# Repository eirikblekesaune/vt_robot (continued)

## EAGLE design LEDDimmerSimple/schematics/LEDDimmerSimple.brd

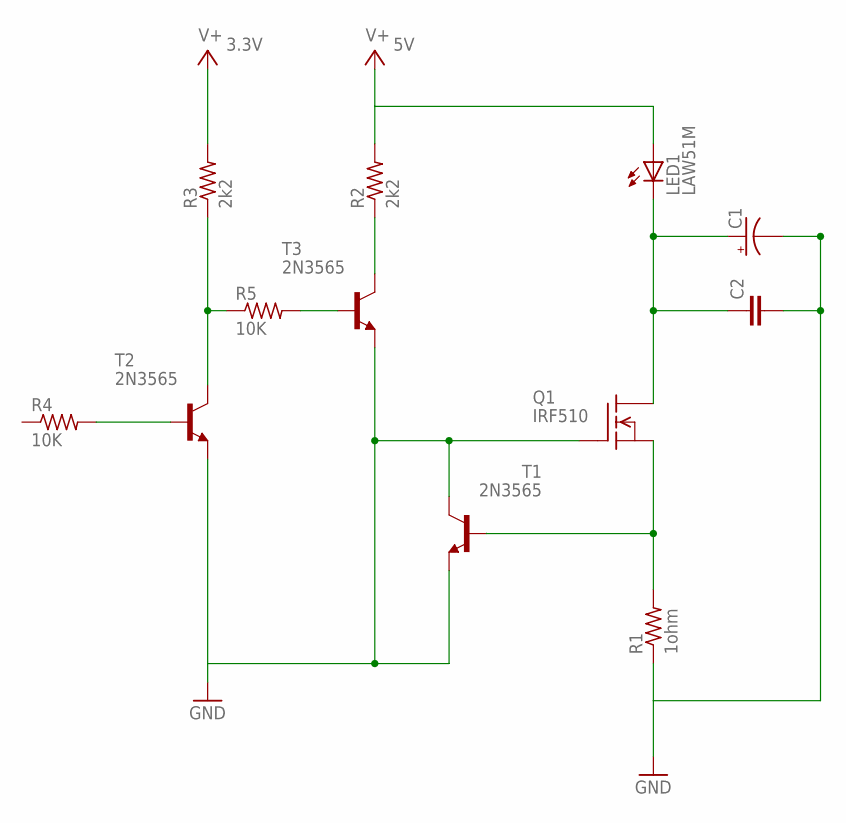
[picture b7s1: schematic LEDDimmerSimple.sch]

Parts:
C1: CPOL-USE1.8-4; E1,8-4
C2: C-EU025-030X050; C025-030X050
LED1: LAW51M; W51
Q1: IRF510; TO220
R1: 1ohm; P0613V
R2, R3: 2k2; 0207/7
R4, R5: 10K; 0207/7
T1, T2, T3: 2N3565; TO92

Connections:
GND: C1.-, C2.2, Q1.1 (G), R1.1, T1.1 (C), T1.3 (E), T2.3 (E), T3.3 (E)
unnamed: R3.1, R5.1, T2.1 (C)
unnamed: R4.2, T2.2 (B)
unnamed: R5.2, T3.2 (B)
unnamed: R2.1, T3.1 (C)
unnamed: C1.+, C2.1, LED1.C, Q1.2 (D)
unnamed: Q1.3 (S), R1.2, T1.2 (B)
V+: LED1.A, R2.2, R3.2

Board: 2 copper layers, 12 parts (0 on the bottom side), 8 nets, no tracks yet.

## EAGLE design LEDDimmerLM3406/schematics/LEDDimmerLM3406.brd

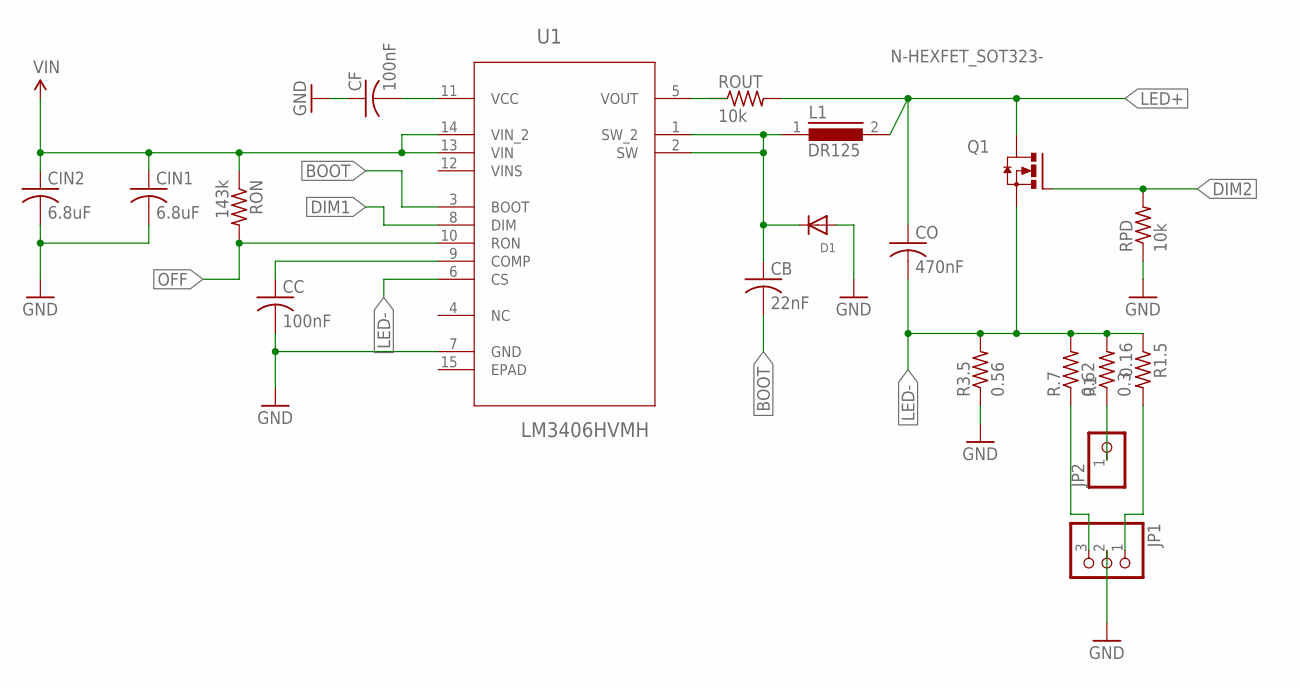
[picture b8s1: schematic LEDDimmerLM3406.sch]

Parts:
CB: 22nF; C0603
CC: 100nF; C0603
CF: 100nF; C0603
CIN1, CIN2: 6.8uF; C1812
CO: 470nF; C1206
D1: DIODESMA; SMADIODE
JP1: PINHD-1X3; 1X03
JP2: PINHD-1X1; 1X01
L1: DR125
Q1: N-HEXFET_SOT323-; SOT223
R1: 0.3; R0805
R1.5: 0.16; R0805
R3.5: 0.56; R0805
R.7: 0.62; R0805
RON: 143k; R0805
ROUT: 10k; R0603
RPD: 10k; R0603
U1: LM3406HVMH; SOP65P640X110-15N

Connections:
BOOT: CB.2, U1.3 (BOOT)
DIM1: U1.8 (DIM)
DIM2: Q1.1 (G), RPD.2
GND: CC.2, CF.1, CIN1.2, CIN2.2, D1.A, JP1.2, R3.5.1, RPD.1, U1.7 (GND)
LED+: CO.1, L1.2, Q1.4 (D), ROUT.2
LED-: CO.2, Q1.3 (S), R1.2, R1.5.1, R3.5.2, R.7.2, U1.6 (CS)
unnamed: CC.1, U1.9 (COMP)
unnamed: CF.2, U1.11 (VCC)
unnamed: CB.1, D1.C, L1.1, U1.1 (SW_2), U1.2 (SW)
unnamed: JP1.3, R.7.1
unnamed: JP1.1, R1.5.2
unnamed: JP2.1, R1.1
OFF: RON.2, U1.10 (RON)
VIN: CIN1.1, CIN2.1, RON.1, U1.13 (VIN), U1.14 (VIN_2)

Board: 2 copper layers, 19 parts (0 on the bottom side), 13 nets, no tracks yet.

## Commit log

2013-04-03 First commit of Arduino sketches
2013-04-03 first pinne commit
2013-04-03 Moved pinne robot into own folder
2013-04-03 Added .gitignore
2013-04-03 Removed useless DS_Store
2013-04-24 bird two with drv8825 stepper and OSC working
2013-04-24 Added lib folder for external libraries
2013-07-08 Started working on new pinnerobot code.
2013-07-08 Only need two byte for value messages
2013-07-09 Update for working with pinnerobot
2013-07-09 Deleted old unused files
2013-07-09 Backup after tragic crash..
2013-07-09 Restoration after crash.
2013-07-09 Added get handlers for left motor commands
2013-07-09 PinneRobot: Fixed direction setting and sematics
2013-07-10 Moving motors into separate classes
2013-07-10 Migrating into C++ style
2013-07-10 Deleted unused files
2013-07-10 Sync before merge
2013-07-10 Backing up files
2013-07-10 Nuther backup
2013-07-10 Removing unused files.
2013-07-10 Fixed:Starting and stoping left motors
2013-07-10 Changed debugging to macros.
2013-07-10 PinneRobot: Reply to get commands
2013-08-13 Moved PinneProtocol.md file
2013-08-13 Updated protocol doc, added parser/api for SC
2013-08-14 API comm with getter and setters. closes #2
2013-08-14 Enabled state change reporting aggin
2013-08-14 Removed and remapped current sense pins for VNH5019 driver.
2013-08-19 Changed defines to consts
2013-09-06 Added pinne and tog patch and classes for monsterbox
2013-09-06 Changed input scaling for pinner og tog. Added one wrieless LED
2013-09-09 An update in case Arduino.app want do somethin awful again.
2013-09-09 Please enter the commit message for your changes. Lines starting PinneMotor logic now works.
2013-09-10 Added rotation motor control with high freq PWM on timer3
2013-09-10 Update on rotation motor implementation. Still to figure the logic for bounds checking and target stopping.
2013-09-17 Added lots of stuff. In two files. Which in not a of stuff.. These commit messages are really testing my creativity.
2013-09-17 Added LEDDimmer fade sketch
2013-09-18 More fixes on the pinnne trobot. Rotation logic almost in place.
2013-09-18 Rotation motor logic in pinnerobot now works, but untested.
2013-09-18 Allow setting currentPosition for pinne motors, since they are relative.
2013-09-18 Failed attempt to add EEPROM setting storage.
2013-09-20 Added OSC responder for fuglen.
2013-09-20 Logic for pinnerobot now works. Still some hickups with starting in park position.
2013-09-20 Started implementing PID control for rotation motor in pinne robot
2013-09-22 Added API and setter/getters for PID control parameters.
2013-09-22 Removed PID control in pinne robot and started implementing standard ease inout class.
2013-09-23 Backup, table lookup sine ramping for targeting in robot pinne
2013-09-23 Some kind of ease ramping function for motors in pinne robot
2013-09-23 Fixed stupid little bug.
2013-09-23 Last update for the evening
2013-09-30 Started making class for pinne robot
2013-10-01 Backup
2013-10-15 Pre merge commit Bontelabo
2013-10-15 Bontalabo update day 2
2013-10-15 Found correct serial port addresses for pinner,
2013-10-27 Bontelabo update for pinner
2013-10-27 Backup before leaving Bontelabo
2013-11-18 Small update to pinne protocol
2013-11-18 Added lokomotiv folder
2013-12-05 Moved PinneRobot project into ino project
2013-12-06 KampenTokyo update
2013-12-06 Added configuration seup to pinne arduino prject
2013-12-06 Text reformatting of robot SC classes
2013-12-07 Added different debounce for slack and top sensor
2013-12-07 Som work on pinne SC classes
2013-12-22 Initial Kopprobot commit
2013-12-22 .gitignore for KoppRobot
2013-12-22 gitignore removals
2013-12-23 Added outline structure
2014-01-09 New year update 2014
2014-01-17 Lokootiv can now parse IR incoming adrres
2014-01-17 .swo removal
2014-01-27 Filename change
2014-02-11 Added schematics for three robots: Kopp, Lokomotiv and IRBeacon
2014-02-11 Added two LED dimmer schematics
2014-03-03 Pinne fixes
2014-03-03 Basic funcationalit for new pinne classes
2014-04-01 More pinne fix and circuit stuff
2014-04-01 Deleted old version of IRBeacon
2014-04-13 gitignore chagne
2014-04-13 EnkelFugl and some circuit changes
2014-04-14 Clasifiing fugle and stepper classes
2014-04-14 Removed DSStore file
2014-04-14 Chassis label for Kopprrobot
2014-04-15 Bugsquashing
2014-04-22 First workin IRBeacon version with etched circuit
2014-04-22 No hex or elf files in rep
2014-04-22 Changes and additions etc.
2014-04-30 Fixed clock setting
2014-04-30 PRe new Kopp roboter
2014-05-02 Added kopp robot simple with walk in mekanikkpatch
2014-05-06 Added fotbrett scehmatic
2014-05-06 Fixed inverting port vals in IRBeaocn
2014-05-06 Fxied invertion IRBeacon again
2014-05-09 Some work on Lokomotiv. Speed interpolation.
2014-05-21 XBeeProfiles for xctung application
2014-05-21 Updates in general
2014-05-21 Converted Lokomtiv t XBee communcation based class
2014-05-27 Implemening peripheral communication by TWI
2014-05-27 Remaking TWI implementation and added dip switch parser LEDDimmerSimple.
2014-05-27 Removed old sway VIM file
2014-05-27 Schematics for new dual LED dimmer with ATtiny4313
2014-05-27 Initilat Pens commit
2014-05-29 New robot HvitFugleRobot
2014-05-29 More work on the LEDDimmmer
2014-05-29 Removed temp file
2014-05-29 Backup comit
2014-06-02 Prescaler fix.
2014-06-02 STarted modularizing files for mekanikkpatch
2014-06-06 Fixing fault in node discover parsing. Modularizing Mekanikkpatch
2014-06-06 Some fixes.
2014-06-06 Preparing for tracking test1
2014-06-06 Some fies in mekanikk modules
2014-06-09 Added Lokomotiv polling for distance
2014-06-09 Lokomotiver update
2014-06-09 Increased coordinator XBee baudrate to 115200
2014-06-10 MEr lok fix
2014-06-13 PRe Hedda backup
2014-06-13 Remove Ali from Actorcontrol
2014-06-23 Fixed missing update call and set speedeometer to signed lngs
2014-06-23 Correncted tog TO parsing and added setting network route aggregation for corrdinartori
2014-06-23 Measuring speed by ticks per 10th millisecond
2014-06-24 Added PID speed cruise control
2014-06-24 Lokomotiv encoder isr optimizing
2014-06-25 After good tracking test
2014-06-25 Dynamic tuning of PID parameters for better correction of larger error amounts
2014-06-25 Lokomotiv:Turning off cruise control properly when motorMode is changed
2014-06-27 Lokomotiv: Ensure that motor stops under cruise control. Closes #19
2014-06-27 Lokomotiv: Made direct binding to XBee proxy module instead of coordinator indirection.
2014-06-27 Lokomotiver patch:Removed some uneccesary code
2014-06-27 Remove debug code
2014-06-27 Fixed bug where PID algorithm din't get updated values on output
2014-06-27 Using stop as stop message,rathert than speed to 0
2014-06-27 Fixed incorrect name getter in VTLokomotiv
2014-07-07 Small change
2014-07-07 Update befre merge and new system test for lokomotiv
2014-07-07 Update after suceessful tracking tests
2014-07-08 Moved control over to Asle fader boxes. Fixed stop to fader update. Tracking functionalitey into lomomotiv patch
2014-07-08 Added OSC responders for calibrating and activating tracking for lokomotiv
2014-07-08 Added only update on changed distance for lokomotiv
2014-07-08 More fixes for tracking
2014-07-12 First commit for LEDDimmerDuMini
2014-07-12 Ignoring build folder
2014-07-12 Removed build files for nontracking
2014-07-12 Added TWI request
2014-07-12 Added peripheral set and peripheralrequests
2014-07-13 LEDdimmerDuoMini: Fading funcionality
2014-07-13 Loading TWI address upon init and hidden address offset
2014-07-13 Lokomotiv and LEDDimmerDuoMini got reqeuste responders functions
2014-07-13 Made lookup curve. Will implemet this in SC application rather than on the MCU
2014-07-13 Begun working on scehmtaics for LEDDimmerDUMini
2014-07-14 Update before LED flaate testen
2014-07-14 Fixed push start lokomotiv bug
2014-07-17 Backup before lightning
2014-07-18 Test fir flashing on stage
2014-07-18 Now with hardcoded video trackin glokomotiv
2014-07-18 Moved tallerken patch to flaate Mac
2014-07-19 Finished laying out components for LEEDDimmerDuoM<ini
2014-07-19 Last fiz in prod for Lokomotiv. hopefully
2014-07-19 Small update
2014-08-13 Tracking update
2014-08-20 Trakcing, kranser,soundAttach update
2014-08-25 Ignoring .swl
2014-08-25 Backups and update and stuff
2014-08-25 Name changes
2014-08-25 Even more renaming
2014-08-26 Started schematic for ServoCity
2014-08-26 Fixed faulty scematic for LEDDimmerDuoMini
2014-08-30 Backup before moving to HOK
2014-09-07 Henia Onstad backup
2014-09-09 Actorcontrol update
2014-11-04 mini3 post HOK update
2014-11-04 Flatte mac post HOK update
2014-11-05 HOK post laptop update
2014-11-16 Changed gitignore and annual
2015-01-07 Cleaning up pinne robot code for trailing whitespace and replacing leading spaces with tabs
2015-01-07 Code cleanup tabs and spaces etc
2015-01-07 Ignoring tags files from ctags
2015-01-07 KoppRobot code cleanup
2015-01-07 Lokomotiv code cleanup
2015-03-03 Test file for lokomotiv with wifi
2015-03-03 Woring with WIFI Lokomotiv now
2015-03-10 Lokomotiv WIFI can now test. Moving some files
2015-03-10 Ignoring tags files
2015-03-10 Changed pinne test
2015-03-10 Wifi lokomotiv testing
2015-03-11 Testing mode for Lokomotiv
2015-03-13 Before WIFI move
2015-03-14 Fixed WIFI lokomotiv parsing and set/get
2015-03-27 PinneRobot:No delay in loop func
2015-03-27 PinneRobot Using max speed as rotation parking
2015-03-31 Prioer upload master merged wifiLokomotiv
2015-04-01 WifiLokomotiv now responds with proper state change updates, and bi[olarspeed is now the only way to control motor
2015-04-02 New target speed mode for lokomotiv
2015-04-02 Dont stops interrupts when geting pinne current positions
2015-04-02 Shorter debounce for top sensor pinne, ignoring the signals from slack sensor pinne.
2015-04-07 Elisabeth control changed
2015-04-08 Added clock calibration API for lokomotiv wifi
2015-04-12 send timestamp with tracking data
2015-04-27 Made pense box code. Not tested but compiles.
2015-05-08 Filedelete
2015-05-20 Small kopp code cleanup
2015-05-20 KoppRobot:Remove intertup stop when getitng current positions, shorten stop button debounce time
2015-05-20 Retabbing
2015-06-02 Fixed stopAtTarget for cruisecontrol motormode. Close #65
2015-06-02 Fixed bug where lokomotiv didn't interpolate speed i targetSpeed mode
2015-06-02 Prevent stopping lokomotiv with interpolation when already stopped. Close blacksound/VTModularNetwork#68
2015-06-03 Updated lokomotic wifi XBee settings
2015-07-08 Backup dirty update shit
2015-10-03 New mini monster box code
2017-12-30 Ignore vscode hidden files
